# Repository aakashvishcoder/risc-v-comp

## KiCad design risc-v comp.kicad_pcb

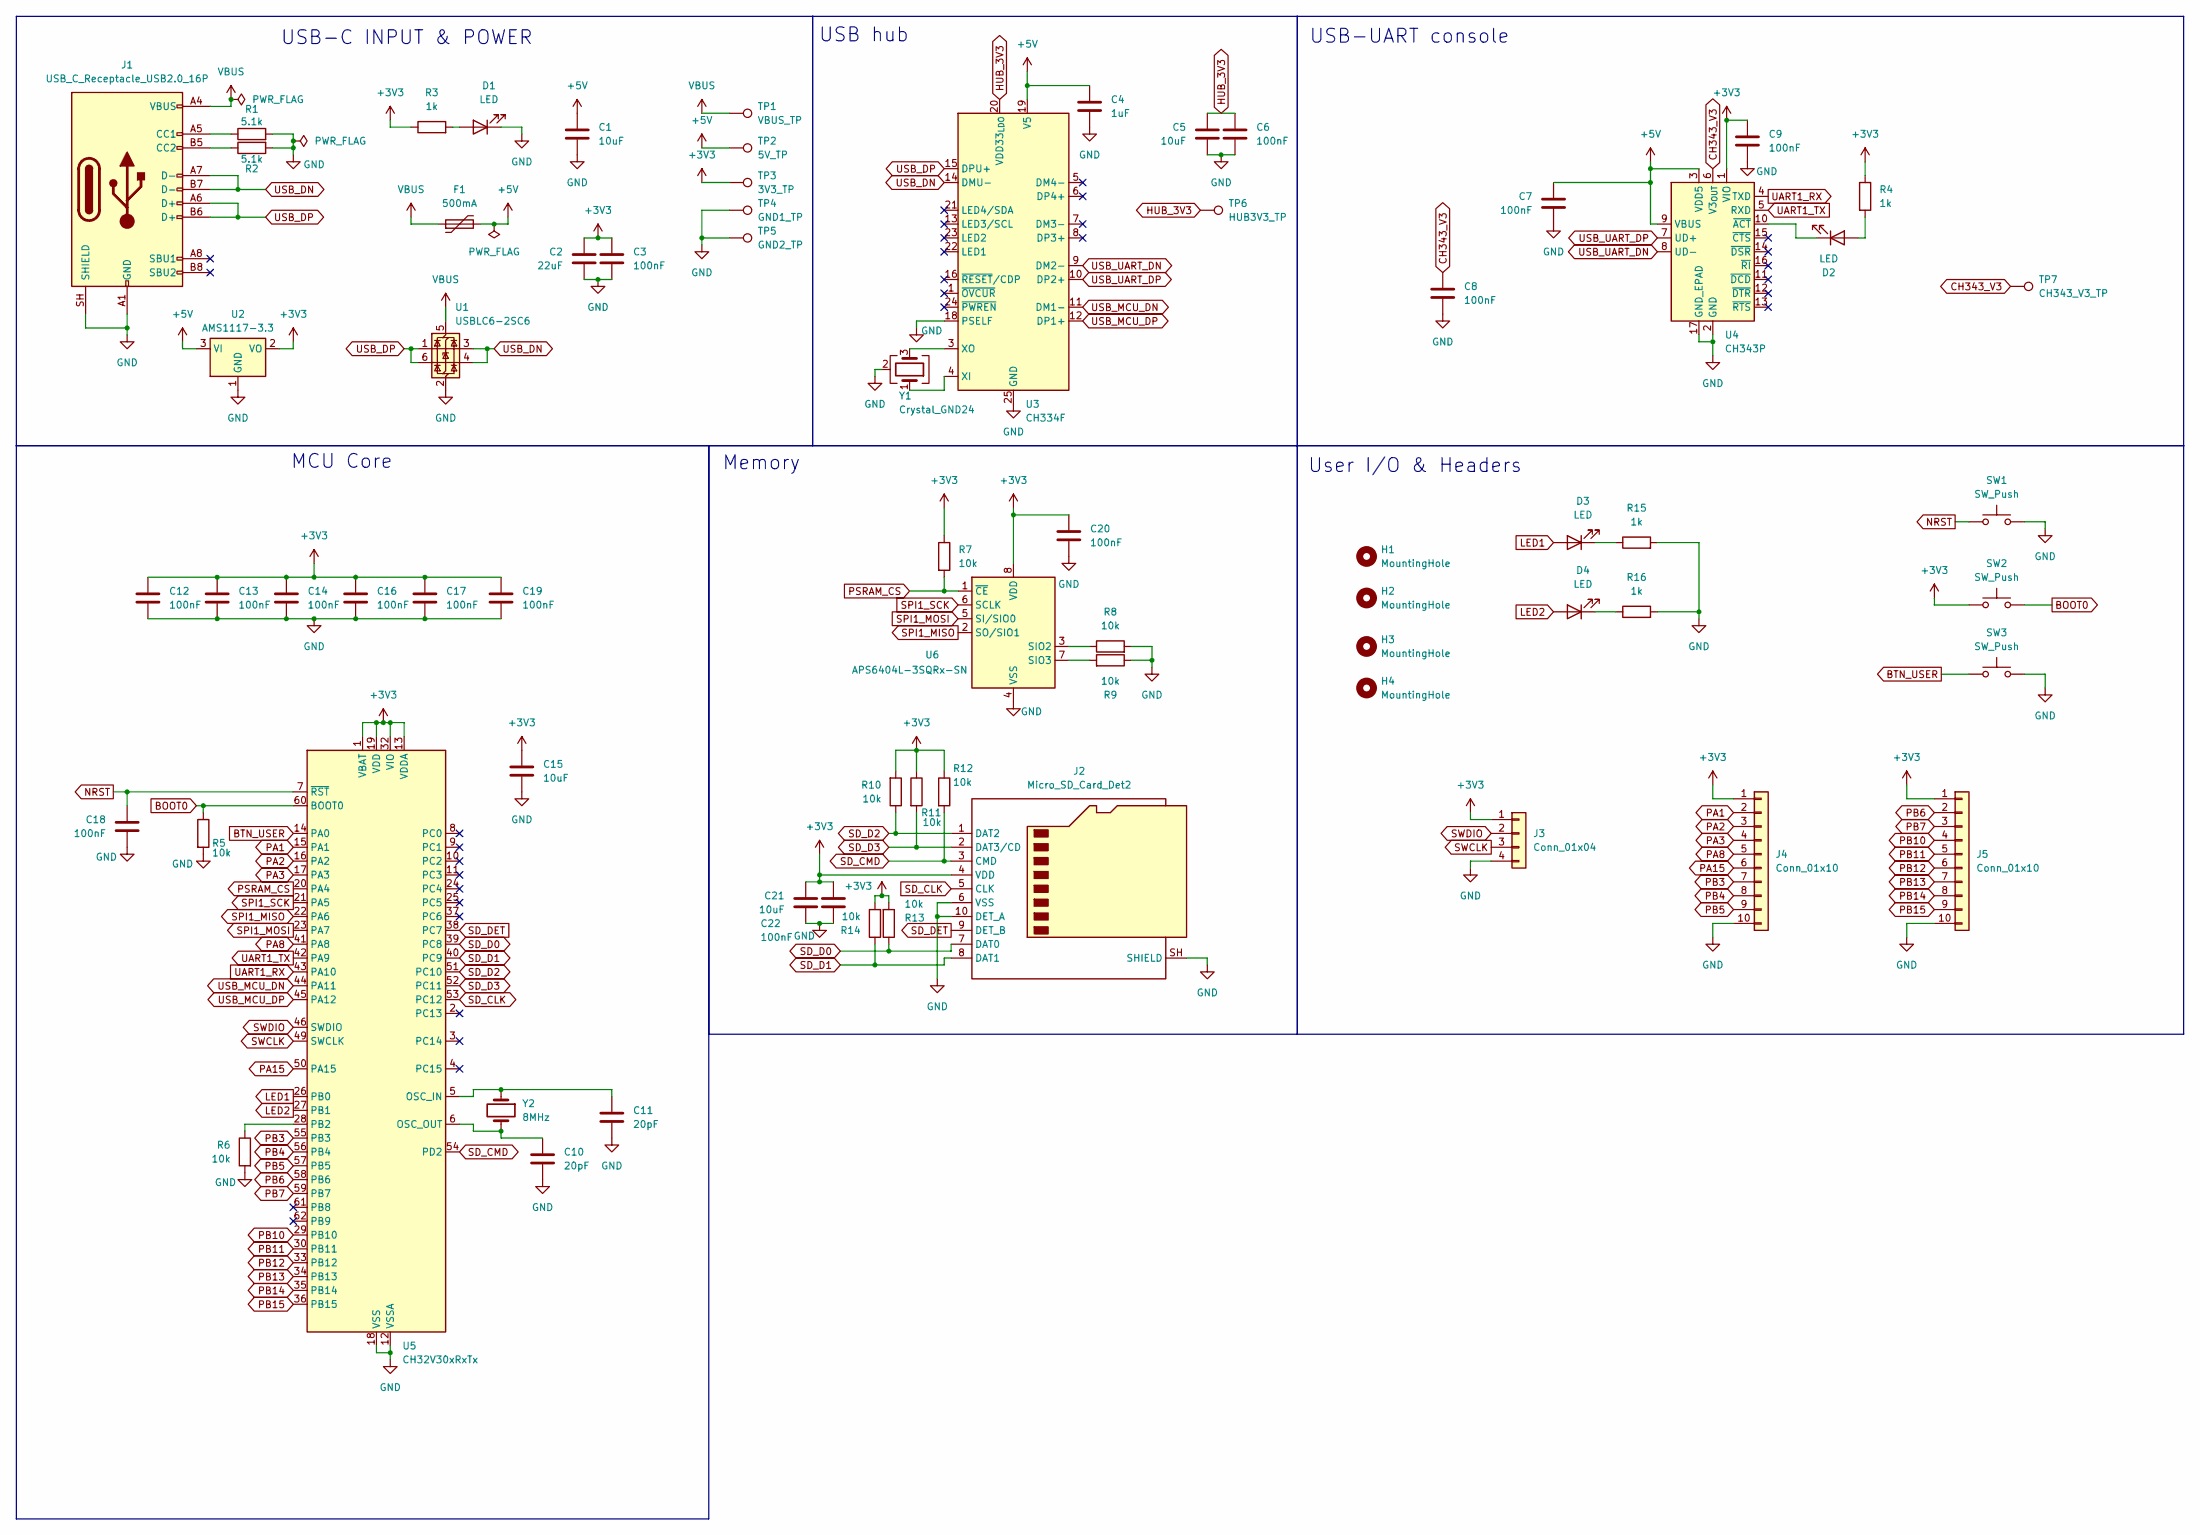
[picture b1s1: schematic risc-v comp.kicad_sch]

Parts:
C1, C5, C15, C21: 10uF; C_0603_1608Metric; LCSC C19702
C2: 22uF; C_0805_2012Metric; LCSC C45783
C3, C6, C7, C8, C9, C12, C13, C14, C16, C17, C18, C19, C20, C22: 100nF; C_0402_1005Metric; LCSC C1525
C4: 1uF; C_0402_1005Metric; LCSC C52923
C10, C11: 20pF; C_0402_1005Metric; LCSC C1554
D1, D2, D3, D4: LED; LED_0603_1608Metric; LCSC C2286
F1: 500mA; Fuse_0805_2012Metric; LCSC C20978
H1, H2, H3, H4: MountingHole; MountingHole_2.7mm_M2.5
J1: USB_C_Receptacle_USB2.0_16P; USB_C_Receptacle_HRO_TYPE-C-31-M-12; LCSC C165948
J2: Micro_SD_Card_Det2; microSD_HC_Molex_104031-0811; LCSC C585350
J3: Conn_01x04; PinHeader_1x04_P2.54mm_Vertical; LCSC C2337
J4, J5: Conn_01x10; PinHeader_1x10_P2.54mm_Vertical; LCSC C2337
R1, R2: 5.1k; R_0402_1005Metric; LCSC C25905
R3, R4, R15, R16: 1k; R_0402_1005Metric; LCSC C11702
R5, R6, R7, R8, R9, R10, R11, R12, R13, R14: 10k; R_0402_1005Metric; LCSC C25744
SW1, SW2, SW3: SW_Push; SW_Push_1P1T_XKB_TS-1187A; LCSC C318884
TP1: VBUS_TP; TestPoint_Pad_D1.5mm
TP2: 5V_TP; TestPoint_Pad_D1.5mm
TP3: 3V3_TP; TestPoint_Pad_D1.5mm
TP4: GND1_TP; TestPoint_Pad_D1.5mm
TP5: GND2_TP; TestPoint_Pad_D1.5mm
TP6: HUB3V3_TP; TestPoint_Pad_D1.5mm
TP7: CH343_V3_TP; TestPoint_Pad_D1.5mm
U1: USBLC6-2SC6; SOT-23-6; LCSC C7519
U2: AMS1117-3.3; SOT-223-3_TabPin2; LCSC C6186
U3: CH334F; QFN-24-1EP_4x4mm_P0.5mm_EP2.7x2.7mm; LCSC C5187527
U4: CH343P; WCH_QFN-16-1EP_3x3mm_P0.5mm_EP1.8x1.8mm; LCSC C2846043
U5: CH32V30xRxTx; LQFP-64_10x10mm_P0.5mm; LCSC C2988083
U6: APS6404L-3SQRx-SN; SOIC-8_3.9x4.9mm_P1.27mm; LCSC C5333729
Y1: Crystal_GND24; Crystal_SMD_3225-4Pin_3.2x2.5mm; LCSC C9002
Y2: 8MHz; Crystal_SMD_5032-2Pin_5.0x3.2mm; LCSC C115962

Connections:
+3V3: C2.1, C3.1, C9.1, C12.1, C13.1, C14.1, C15.1, C16.1, C17.1, C19.1, C20.1, C21.1, C22.1, J2.4 (VDD), J3.1, J4.1, J5.1, R3.1, R4.1, R7.1, R10.2, R11.1, R12.1, R13.2, R14.2, SW2.1, TP3.1 (1_1), U2.2 (VO), U4.1 (VIO), U5.1 (VBAT), U5.13 (VDDA), U5.19 (VDD), U5.32 (VIO), U5.48 (VDD), U5.64 (VIO), U6.8 (VDD)
+5V: C1.1, C4.1, C7.1, F1.2, TP2.1 (1_1), U2.3 (VI), U3.19 (V5), U4.3 (VDD5), U4.9 (VBUS)
BOOT0: R5.1, SW2.2, U5.60 (BOOT0)
BTN_USER: SW3.1, U5.14 (PA0)
CH343_V3: C8.1, TP7.1 (1_1), U4.6 (V3_{OUT})
GND: C1.2, C2.2, C3.2, C4.2, C5.2, C6.2, C7.2, C8.2, C9.2, C10.1, C11.2, C12.2, C13.2, C14.2, C15.2, C16.2, C17.2, C18.2, C19.2, C20.2, C21.2, C22.2, D1.1 (K), J1.A1 (GND), J1.A12 (GND), J1.B1 (GND), J1.B12 (GND), J1.SH (SHIELD), J2.6 (VSS), J2.10 (DET_A), J2.SH (SHIELD), J3.4, J4.10, J5.10, R1.2, R2.2, R5.2, R6.2, R8.2, R9.1, R15.2, R16.2, SW1.2, SW3.2, TP4.1 (1_1), TP5.1 (1_1), U1.2 (GND), U2.1 (GND), U3.18 (PSELF), U3.25 (GND), U4.2 (GND), U4.17 (GND_EPAD), U5.12 (VSSA), U5.18 (VSS), U5.31 (VSS), U5.47 (VSS), U5.63 (VSS), U6.4 (VSS), Y1.2 (G), Y1.4 (G)
HUB_3V3: C5.1, C6.1, TP6.1 (1_1), U3.20 (VDD33_{LDO})
LED1: D3.2 (A), U5.26 (PB0)
LED2: D4.2 (A), U5.27 (PB1)
NRST: C18.1, SW1.1, U5.7 (~RST)
unnamed: D1.2 (A), R3.2
unnamed: D2.2 (A), R4.2
unnamed: D2.1 (K), U4.10 (~ACT)
unnamed: D3.1 (K), R15.1
unnamed: D4.1 (K), R16.1
unnamed: J1.A5 (CC1), R1.1
unnamed: J1.B5 (CC2), R2.1
unnamed: U3.4 (XI), Y1.1
unnamed: U3.3 (XO), Y1.3
unnamed: C11.1, U5.5 (OSC_IN), Y2.1
unnamed: C10.2, U5.6 (OSC_OUT), Y2.2
unnamed: R6.1, U5.28 (PB2)
unnamed: R8.1, U6.3 (SIO2)
unnamed: R9.2, U6.7 (SIO3)
PA1: J4.2, U5.15 (PA1)
PA2: J4.3, U5.16 (PA2)
PA3: J4.4, U5.17 (PA3)
PA8: J4.5, U5.41 (PA8)
PA15: J4.6, U5.50 (PA15)
PB3: J4.7, U5.55 (PB3)
PB4: J4.8, U5.56 (PB4)
PB5: J4.9, U5.57 (PB5)
PB6: J5.2, U5.58 (PB6)
PB7: J5.3, U5.59 (PB7)
PB10: J5.4, U5.29 (PB10)
PB11: J5.5, U5.30 (PB11)
PB12: J5.6, U5.33 (PB12)
PB13: J5.7, U5.34 (PB13)
PB14: J5.8, U5.35 (PB14)
PB15: J5.9, U5.36 (PB15)
PSRAM_CS: R7.2, U5.20 (PA4), U6.1 (~CE)
SD_CLK: J2.5 (CLK), U5.53 (PC12)
SD_CMD: J2.3 (CMD), R12.2, U5.54 (PD2)
SD_D0: J2.7 (DAT0), R13.1, U5.39 (PC8)
SD_D1: J2.8 (DAT1), R14.1, U5.40 (PC9)
SD_D2: J2.1 (DAT2), R10.1, U5.51 (PC10)
SD_D3: J2.2 (DAT3/CD), R11.2, U5.52 (PC11)
SD_DET: J2.9 (DET_B), U5.38 (PC7)
SPI1_MISO: U5.22 (PA6), U6.2 (SO/SIO1)
SPI1_MOSI: U5.23 (PA7), U6.5 (SI/SIO0)
SPI1_SCK: U5.21 (PA5), U6.6 (SCLK)
SWCLK: J3.3, U5.49 (SWCLK)
SWDIO: J3.2, U5.46 (SWDIO)
UART1_RX: U4.4 (TXD), U5.43 (PA10)
UART1_TX: U4.5 (RXD), U5.42 (PA9)
USB_DN: J1.A7 (D-), J1.B7 (D-), U1.3 (I/O2), U1.4 (I/O2), U3.14 (DMU-)
USB_DP: J1.A6 (D+), J1.B6 (D+), U1.1 (I/O1), U1.6 (I/O1), U3.15 (DPU+)
USB_MCU_DN: U3.11 (DM1-), U5.44 (PA11)
USB_MCU_DP: U3.12 (DP1+), U5.45 (PA12)
USB_UART_DN: U3.9 (DM2-), U4.8 (UD-)
USB_UART_DP: U3.10 (DP2+), U4.7 (UD+)
VBUS: F1.1, J1.A4 (VBUS), J1.A9 (VBUS), J1.B4 (VBUS), J1.B9 (VBUS), TP1.1 (1_1), U1.5 (VBUS)

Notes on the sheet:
USB-UART console
USB hub
User I/O & Headers
Memory
MCU Core
USB-C INPUT & POWER

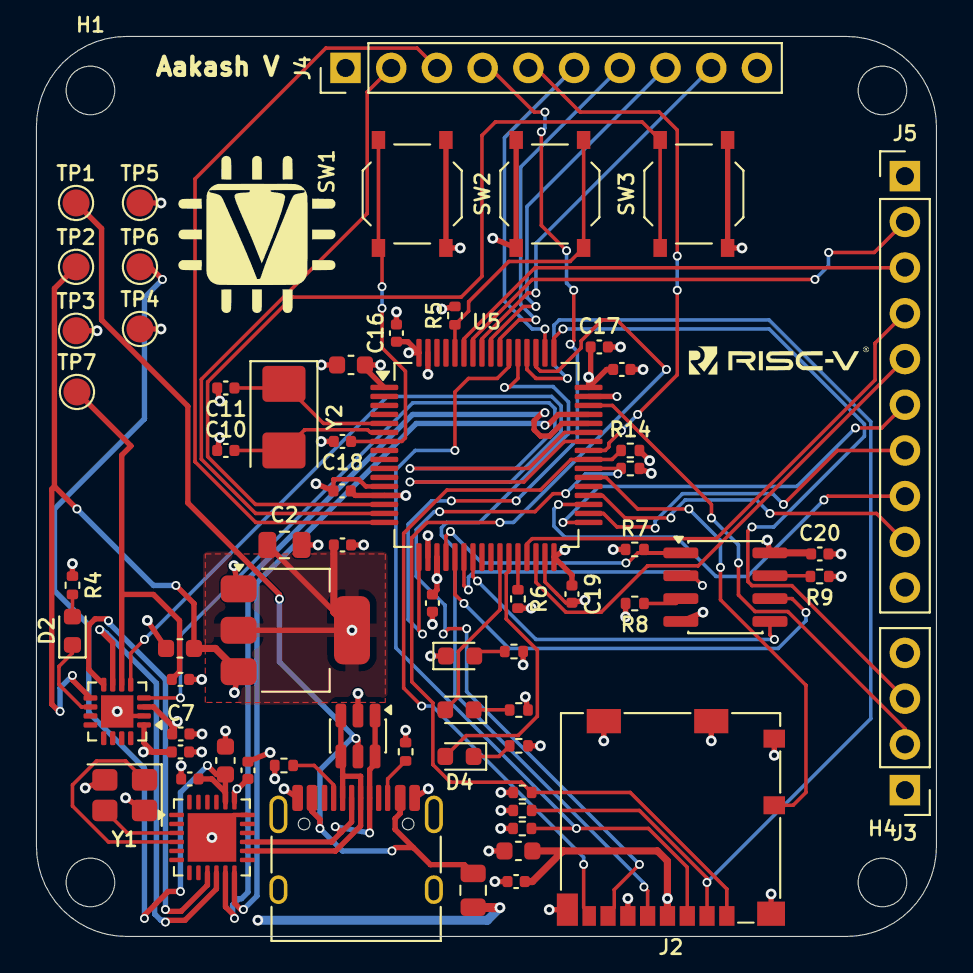
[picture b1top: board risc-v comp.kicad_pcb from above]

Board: 4 copper layers, 50.0 x 50.0 mm, 70 parts (0 on the bottom side), 62 nets.

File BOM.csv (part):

Section,Ref (planned),Qty/board,Value / Description,Manufacturer Part,LCSC #,JLC Type,Package,KiCad Symbol,KiCad Footprint,Unit Price (USD),Assembled By,Notes
1 USB-C & Power,J1,1,USB-C receptacle USB2.0 16-pin,TYPE-C-31-M-12 (HRO),C165948,Extended,SMD,Connector:USB_C_Receptacle_USB2.0_16P,Connector_USB:USB_C_Receptacle_HRO_TYPE-C-31-M-12,0.19,JLC,322k in stock
1 USB-C & Power,"R1,R2",2,5.1k 1% 0402 (CC pull-downs),0402WGF5101TCE,C25905,Basic,0402,Device:R,Resistor_SMD:R_0402_1005Metric,0.002,JLC,Tells the host we are a USB device (sink)
1 USB-C & Power,U1,1,USB ESD protection,USBLC6-2SC6 (ST),C7519,Extended,SOT-23-6,Power_Protection:USBLC6-2SC6,Package_TO_SOT_SMD:SOT-23-6,0.16,JLC,Clones C2687116 are $0.05 if you want cheaper
1 USB-C & Power,F1,1,PTC resettable fuse 500mA hold / 1A trip,SMD0805P050TF,C20978,Extended,0805,Device:Polyfuse,Fuse:Fuse_0805_2012Metric,0.07,JLC,Protects your laptop USB port if something shorts
1 USB-C & Power,U2,1,3.3V 1A LDO regulator,AMS1117-3.3,C6186,Basic,SOT-223,Regulator_Linear:AMS1117-3.3,Package_TO_SOT_SMD:SOT-223-3_TabPin2,0.21,JLC,Basic part (no $3 fee). Smaller alt: AP2112K-3.3TRG1 C51118 (SOT-23-5 extended)
1 USB-C & Power,C1,1,10uF 10V X5R 0603 (LDO input),CL10A106KP8NNNC,C19702,Basic,0603,Device:C,Capacitor_SMD:C_0603_1608Metric,0.02,JLC,
1 USB-C & Power,C2,1,22uF 25V X5R 0805 (LDO output),CL21A226MAQNNNE,C45783,Basic,0805,Device:C,Capacitor_SMD:C_0805_2012Metric,0.18,JLC,AMS1117 needs >=22uF on output for stability
1 USB-C & Power,C3,1,100nF 16V X7R 0402,CL05B104KO5NNNC,C1525,Basic,0402,Device:C,Capacitor_SMD:C_0402_1005Metric,0.003,JLC,
1 USB-C & Power,D1,1,Red LED 0603 (power indicator),KT-0603R,C2286,Basic,0603,Device:LED,LED_SMD:LED_0603_1608Metric,0.008,JLC,
1 USB-C & Power,R3,1,1k 1% 0402 (LED resistor),0402WGF1001TCE,C11702,Basic,0402,Device:R,Resistor_SMD:R_0402_1005Metric,0.001,JLC,~1.3mA LED current
1 USB-C & Power,TP1-TP5,5,Test points (VBUS / +5V / +3V3 / GND x2),-,-,-,Bare pad,Connector:TestPoint,TestPoint:TestPoint_Pad_D1.5mm,0,-,Copper pads only; nothing to buy
2 USB Hub,U3,1,USB 2.0 HS 4-port hub (2 ports used),CH334F (WCH),C5187527,Extended,QFN-24 4x4,Interface_USB:CH334F,Package_DFN_QFN:QFN-24-1EP_4x4mm_P0.5mm_EP2.7x2.7mm,0.63,JLC,Swapped from CH334P: CH334F has a stock KiCad symbol. Runs from 5V via internal LDO
2 USB Hub,Y1,1,12MHz crystal 20pF 3225,X322512MSB4SI (YXC),C9002,Basic,SMD3225-4P,Device:Crystal_GND24,Crystal:Crystal_SMD_3225-4Pin_3.2x2.5mm,0.10,JLC,CH334 has built-in ~16pF load caps. Datasheet says no external caps
2 USB Hub,C4,1,1uF 25V X5R 0402 (V5 input),CL05A105KA5NQNC,C52923,Basic,0402,Device:C,Capacitor_SMD:C_0402_1005Metric,0.006,JLC,
2 USB Hub,C5,1,10uF 10V X5R 0603 (VDD33 LDO output),CL10A106KP8NNNC,C19702,Basic,0603,Device:C,Capacitor_SMD:C_0603_1608Metric,0.02,JLC,Datasheet: 0.1uF+10uF on VDD33; bigger cap prevents hub resets on plug-in
2 USB Hub,C6,1,100nF 16V X7R 0402 (VDD33),CL05B104KO5NNNC,C1525,Basic,0402,Device:C,Capacitor_SMD:C_0402_1005Metric,0.003,JLC,
2 USB Hub,TP6,1,Test point (hub internal 3.3V),-,-,-,Bare pad,Connector:TestPoint,TestPoint:TestPoint_Pad_D1.5mm,0,-,Exclude from BOM
3 USB-UART,U4,1,USB to UART bridge (console + serial bootloader),CH343P (WCH),C2846043,Extended,QFN-16 3x3,Interface_USB:CH343P,Package_DFN_QFN:WCH_QFN-16-1EP_3x3mm_P0.5mm_EP1.8x1.8mm,0.98,JLC,No crystal needed (internal clock). Connects to USART1 = MCU bootloader port
3 USB-UART,"C7,C8,C9",3,100nF 16V X7R 0402 (VDD5 / V3 / VIO),CL05B104KO5NNNC,C1525,Basic,0402,Device:C,Capacitor_SMD:C_0402_1005Metric,0.003,JLC,
3 USB-UART,D2,1,Red LED 0603 (console ready indicator),KT-0603R,C2286,Basic,0603,Device:LED,LED_SMD:LED_0603_1608Metric,0.008,JLC,Lights when the computer has set up the serial port (ACT# pin)
3 USB-UART,R4,1,1k 1% 0402 (LED resistor),0402WGF1001TCE,C11702,Basic,0402,Device:R,Resistor_SMD:R_0402_1005Metric,0.001,JLC,
3 USB-UART,TP7,1,Test point (CH343 internal 3.3V),-,-,-,Bare pad,Connector:TestPoint,TestPoint:TestPoint_Pad_D1.5mm,0,-,Exclude from BOM
4 MCU Core,U5,1,RISC-V MCU 144MHz RV32IMAFC 64KB+ SRAM 256KB flash,CH32V307RCT6 (WCH),C2988083,Extended,LQFP-64 10x10,MCU_WCH_RiscV:CH32V30xRxTx,Package_QFP:LQFP-64_10x10mm_P0.5mm,3.46,JLC,1877 in stock. Bootloader on USB + USART1
4 MCU Core,Y2,1,8MHz crystal 20pF (HSE),X50328MSB2GI (YXC),C115962,Basic,SMD5032-2P,Device:Crystal,Crystal:Crystal_SMD_5032-2Pin_5.0x3.2mm,0.25,JLC,Basic (no fee). Smaller 3225 alt: C5181477 (extended)
4 MCU Core,"C10,C11",2,20pF C0G 0402 (crystal load),0402CG200J500NT,C1554,Basic,0402,Device:C,Capacitor_SMD:C_0402_1005Metric,0.002,JLC,Tune later if HSE is off-frequency
4 MCU Core,C12-C18,7,100nF 16V X7R 0402 (VDD x2 / VIO x2 / VDDA / VBAT / NRST),CL05B104KO5NNNC,C1525,Basic,0402,Device:C,Capacitor_SMD:C_0402_1005Metric,0.003,JLC,Datasheet fig 4-1-1: 0.1uF on every VDDx/VIOx/VDDA/VBAT pin
4 MCU Core,C19,1,10uF 10V X5R 0603 (+3V3 bulk at MCU),CL10A106KP8NNNC,C19702,Basic,0603,Device:C,Capacitor_SMD:C_0603_1608Metric,0.02,JLC,
4 MCU Core,"R5,R6",2,10k 1% 0402 (BOOT0 / BOOT1 pull-downs),0402WGF1002TCE,C25744,Basic,0402,Device:R,Resistor_SMD:R_0402_1005Metric,0.003,JLC,BOOT0=0 BOOT1=0 -> run from flash. Hold BOOT button at reset -> bootloader
5 Memory,U6,1,8MB (64Mbit) QSPI PSRAM,APS6404L-3SQR-SN (AP Memory),C5333729,Extended,SOP-8,Memory_RAM:APS6404L-3SQRx-SN,Package_SO:SOIC-8_3.9x4.9mm_P1.27mm,3.99,JLC,Only in-stock PSRAM (ESP-PSRAM64H / LY68L6400 out of stock)
5 Memory,C20,1,100nF 16V X7R 0402 (PSRAM VDD),CL05B104KO5NNNC,C1525,Basic,0402,Device:C,Capacitor_SMD:C_0402_1005Metric,0.003,JLC,
5 Memory,J2,1,microSD socket push-pull,104031-0811 (Molex),C585350,Extended,SMD,Connector:Micro_SD_Card_Det2,Connector_Card:microSD_HC_Molex_104031-0811,0.68,JLC,"Pin 9 DET_B -> SD_DET, pin 10 DET_A -> GND (MCU internal pull-up)"
5 Memory,C21,1,10uF 10V X5R 0603 (SD card bulk),CL10A106KP8NNNC,C19702,Basic,0603,Device:C,Capacitor_SMD:C_0603_1608Metric,0.02,JLC,SD cards pull current spikes on write
5 Memory,R7,1,10k 1% 0402 (PSRAM CE# pull-up),0402WGF1002TCE,C25744,Basic,0402,Device:R,Resistor_SMD:R_0402_1005Metric,0.003,JLC,Holds CE# high during power-up (datasheet sec 7)
5 Memory,"R8,R9",2,10k 1% 0402 (PSRAM SIO2/SIO3 pull-downs),0402WGF1002TCE,C25744,Basic,0402,Device:R,Resistor_SMD:R_0402_1005Metric,0.003,JLC,Unused in SPI mode; datasheet wants them low at power-up
5 Memory,C22,1,100nF 16V X7R 0402 (SD VDD),CL05B104KO5NNNC,C1525,Basic,0402,Device:C,Capacitor_SMD:C_0402_1005Metric,0.003,JLC,
5 Memory,R10-R14,5,10k 1% 0402 (SD CMD/DAT0-3 pull-ups),0402WGF1002TCE,C25744,Basic,0402,Device:R,Resistor_SMD:R_0402_1005Metric,0.003,JLC,No pull-up on CLK
6 User I/O,"D3,D4",2,Red LED 0603 (user LEDs),KT-0603R,C2286,Basic,0603,Device:LED,LED_SMD:LED_0603_1608Metric,0.008,JLC,Red = only in-stock basic LED (green C72043 out of stock)
6 User I/O,"R15,R16",2,1k 1% 0402 (LED resistors),0402WGF1001TCE,C11702,Basic,0402,Device:R,Resistor_SMD:R_0402_1005Metric,0.001,JLC,
6 User I/O,SW1-SW3,3,Tactile switch 5.1x5.1mm SMD (RESET / BOOT / USER),TS-1187A-B-A-B (XKB),C318884,Basic,SMD 5.1x5.1,Switch:SW_Push,Button_Switch_SMD:SW_Push_1P1T_XKB_TS-1187A,0.02,JLC,
6 User I/O,J3,1,1x4 2.54mm header (WCH-LinkE debug: 3V3/SWDIO/SWCLK/GND),2.54-1*40P (break off),C2337,-,THT,Connector_Generic:Conn_01x04,Connector_PinHeader_2.54mm:PinHeader_1x04_P2.54mm_Vertical,0.16,You,One 1x40 strip covers J3-J5
6 User I/O,"J4,J5",2,1x10 2.54mm GPIO headers,2.54-1*40P (break off),C2337,-,THT,Connector_Generic:Conn_01x10,Connector_PinHeader_2.54mm:PinHeader_1x10_P2.54mm_Vertical,(same strip),You,Pin assignment decided in section 6
,,,,,,,,,,,,
COST ESTIMATE (check live at checkout),,,,,,,,,,,,
Parts per board (JLC-assembled),,,,,,,,,,~11,,
Parts for 2 assembled boards (JLC minimum),,,,,,,,,,~22,,
Extended-part fees (8 extended parts x $3),,,,,,,,,,24,,"J1, U1, F1, U3, U4, U5, U6, J2"
PCBA setup + stencil,,,,,,,,,,~10,,
"4-layer PCB, 5 pcs, <= 50x50mm",,,,,,,,,,~8,,
Shipping (JLC economy),,,,,,,,,,~15-25,,
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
